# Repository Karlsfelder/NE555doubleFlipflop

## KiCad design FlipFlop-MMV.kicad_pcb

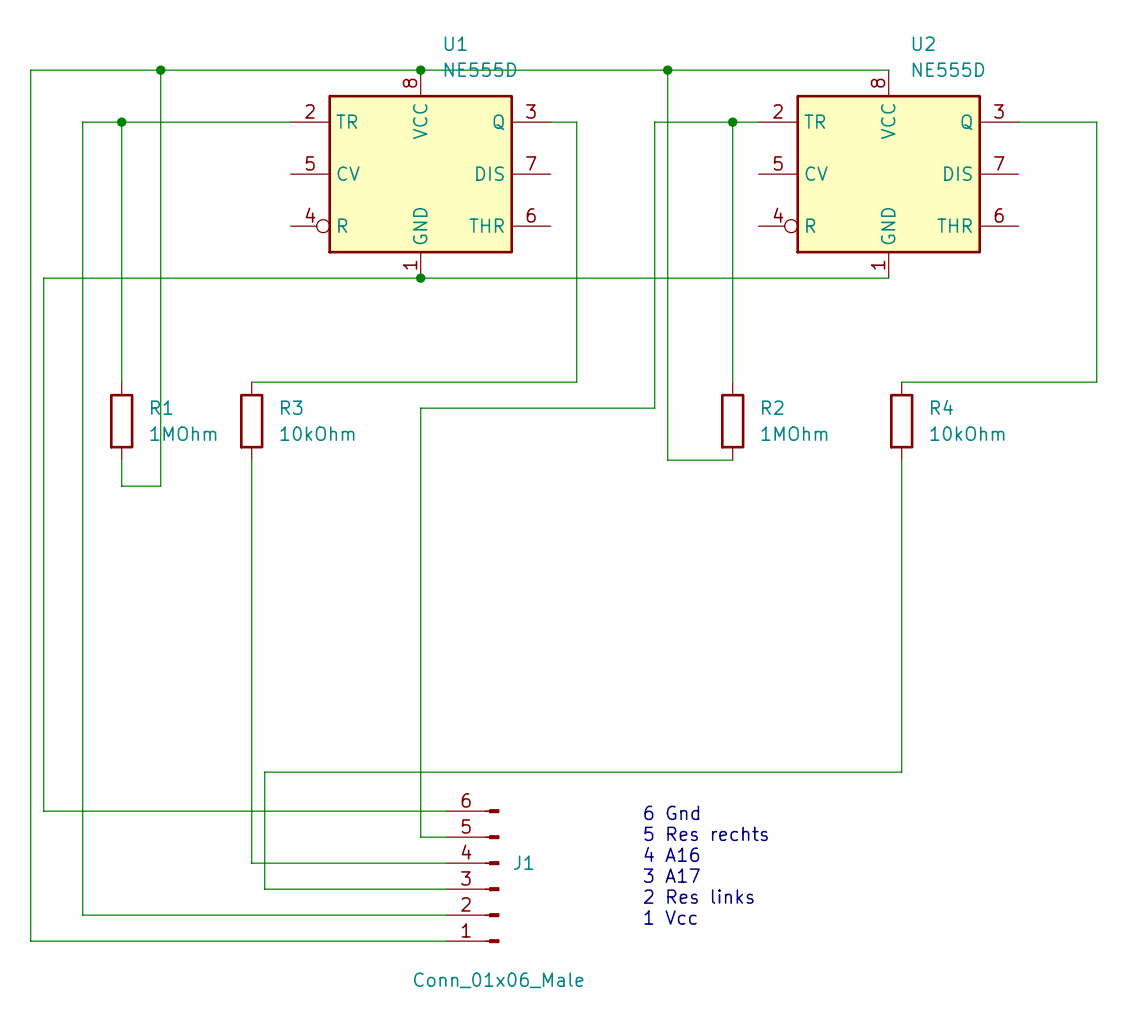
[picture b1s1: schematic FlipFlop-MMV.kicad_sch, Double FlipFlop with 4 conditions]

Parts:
J1: Conn_01x06_Male; PinSocket_2x03_P1.27mm_Vertical_SMD
R1, R2: 1MOhm; R_1206_3216Metric
R3, R4: 10kOhm; R_1206_3216Metric
U1, U2: NE555D; SOIC-8_3.9x4.9mm_P1.27mm

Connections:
unnamed: J1.1, R1.2, R2.2, U1.8 (VCC), U2.8 (VCC)
unnamed: J1.2, R1.1, U1.2 (TR)
unnamed: J1.5, R2.1, U2.2 (TR)
unnamed: R3.1, U1.3 (Q)
unnamed: J1.4, R3.2
unnamed: R4.1, U2.3 (Q)
unnamed: J1.3, R4.2
unnamed: J1.6, U1.1 (GND), U2.1 (GND)

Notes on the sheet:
6 Gnd 5 Res rechts 4 A16 3 A17 2 Res links 1 Vcc

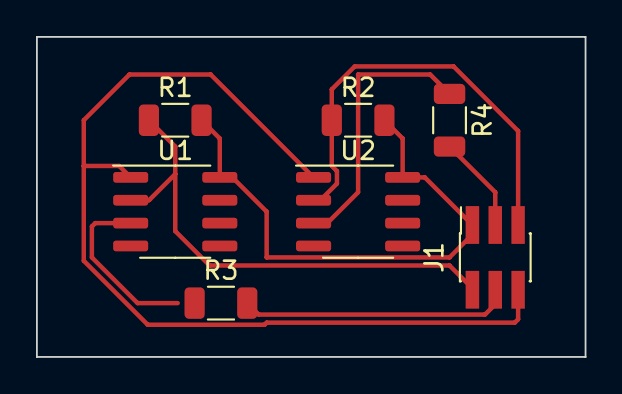
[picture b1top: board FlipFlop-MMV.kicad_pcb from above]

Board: 2 copper layers, 30.5 x 17.8 mm, 7 parts (0 on the bottom side), 8 nets.
